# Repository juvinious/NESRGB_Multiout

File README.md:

# NESRGB_Multiout

NES Multiout for use with Tim Worthington's NES RGB mod v5.

Same FCC connector that NES RGB uses to match up to the main board. The FCC Connector is 18 positions, [LCSC Part #: C262640](https://www.lcsc.com/product-detail/C262640.html?s_z=n_q_AFC07-S18ECA-00&spm=wm.fly.bg.0.xh&lcsc_vid=RlQIVgJfQwVcBlxQQVAKAl0DQ1BdA1ZSFQAIAlwFRlIxVlNeRlNeUFFWRVhcXjsOAxUeFF5JWBYZEEoKFBINSQcJGk4%3D).

**Top**

**Bottom**

## Origin and attribution

This project began as a fork of [zaxour's NESRGB_Multiout](https://github.com/zaxour/NESRGB_Multiout),
which was published without a license. This repository is an independent
re-implementation in KiCad: the design was converted from the original Eagle
files, the layout reworked, and an FFC connector added. The original Eagle
files and the 2021 gerbers are available from zaxour's repository.

## License

Copyright the NESRGB_Multiout contributors.

This source describes Open Hardware and is licensed under the CERN-OHL-S v2
(`CERN-OHL-S-2.0`). See [LICENSE](LICENSE) for the full text.

You may redistribute and modify this source and make products using it under
the terms of the [CERN-OHL-S v2](https://ohwr.org/cern_ohl_s_v2.txt). This
source is distributed WITHOUT ANY EXPRESS OR IMPLIED WARRANTY, INCLUDING OF
MERCHANTABILITY, SATISFACTORY QUALITY AND FITNESS FOR A PARTICULAR PURPOSE.
Please see the CERN-OHL-S v2 for applicable conditions.

Source location: https://github.com/juvinious/NESRGB_Multiout

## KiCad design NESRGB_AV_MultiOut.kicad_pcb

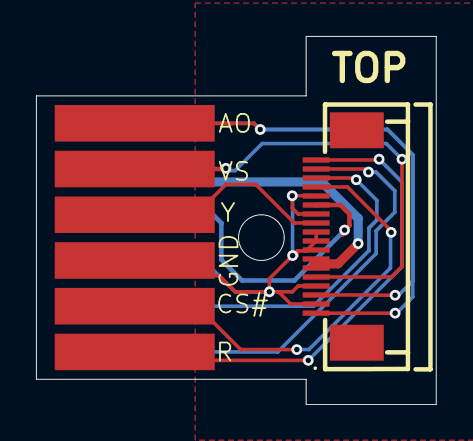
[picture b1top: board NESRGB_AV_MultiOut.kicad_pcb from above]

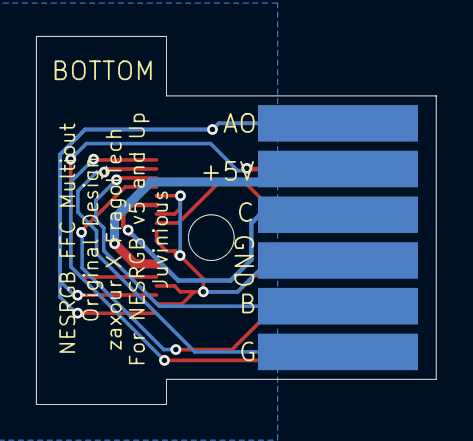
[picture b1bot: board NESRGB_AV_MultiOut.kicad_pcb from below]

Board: 16 copper layers, 22.2 x 20.4 mm, 14 parts (6 on the bottom side), 10 nets.

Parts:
PAD1, PAD2, PAD3, PAD4, PAD5, PAD6, PAD7, PAD8, PAD9, PAD10, PAD11, PAD12: SMD_PADNIN_AV; SMD_NINAV
UNK_HOLE_0: dummyfp0
X1: AFC07-S18ECA-00; C262640_FPC-SMD_AFC07-S18ECA-00

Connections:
/+5V: PAD8.1, X1.+5V
/BLUE: PAD11.1, X1.BLUE
/C: PAD9.1, X1.C
/CSYNC: PAD5.1, X1.CSYNC
/CVBS: PAD2.1, X1.CVBS
/GND: PAD4.1, PAD10.1, X1.GND
/GREEN: PAD12.1, X1.GREEN
/MONO_AUD: PAD1.1, PAD7.1, X1.MONO_AUD
/RED: PAD6.1, X1.RED
/Y: PAD3.1, X1.Y

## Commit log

2026-06-12 Begin organizing project.
2026-06-12 Updated layout for the pcb.
2026-06-12 Further organization, include changes for the ffc connector.
2026-06-12 Create scripts for github ci and for creating fabrication outputs.
2026-06-12 Added license, removed eagle files and references and replaced images with the new board pinout/layout.
2026-06-12 Added checks for erc/drc in github ci. Added badges to README. Cleaned up all erc/drc, all clean.
2026-06-12 Convert to kicad and organize content (#1)
    * Begin organizing project.
    * Updated layout for the pcb.
    * Further organization, include changes for the ffc connector.
    * Create scripts for github ci and for creating fabrication outputs.
    * Added license, removed eagle files and references and replaced images with the new board pinout/layout.
    * Added checks for erc/drc in github ci. Added badges to README. Cleaned up all erc/drc, all clean.
2026-06-12 Generate placement file. Remove pads and hole from export in bom and position files.
2026-06-12 Updated readme to reflect changes.
